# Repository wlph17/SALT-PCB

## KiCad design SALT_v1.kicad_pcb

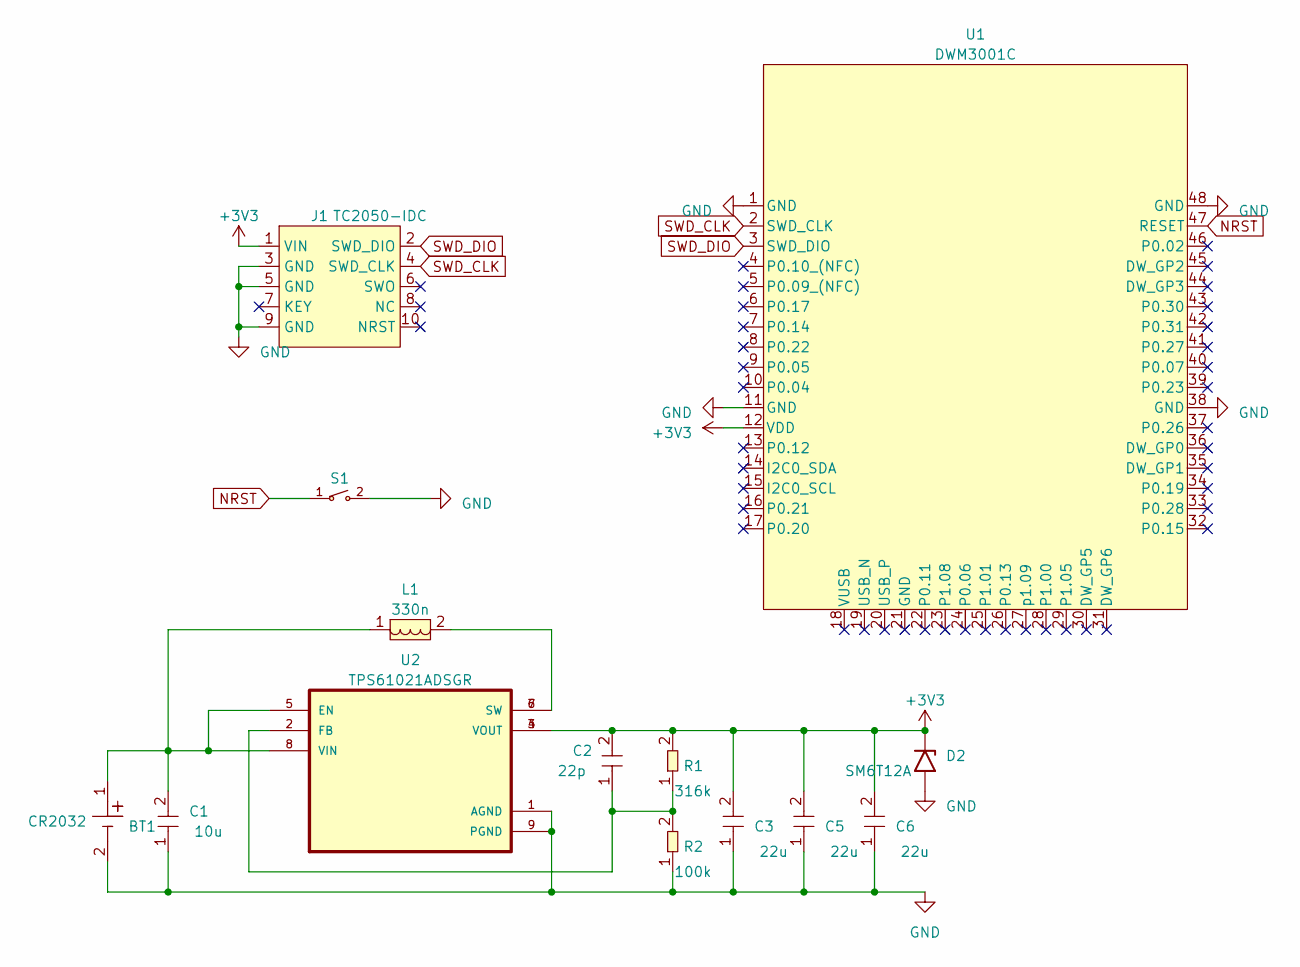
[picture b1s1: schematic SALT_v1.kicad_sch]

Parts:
BT1: CR2032; BAT_BHX1-2032-SM
C1: 10u; C_0603_1608Metric_Pad1.08x0.95mm_HandSolder
C2: 22p; C_0402_1005Metric_Pad0.74x0.62mm_HandSolder
C3, C5, C6: 22u; C_0603_1608Metric_Pad1.08x0.95mm_HandSolder
D2: SM6T12A; D_SMB
J1: TC2050-IDC
L1: 330n; IND_SRP4020TA-R33M
R1: 316k; R_0402_1005Metric_Pad0.72x0.64mm_HandSolder
R2: 100k; R_0402_1005Metric_Pad0.72x0.64mm_HandSolder
S1: SW_RS-032G05A3-SMRT
U1: DWM3001C
U2: TPS61021ADSGR

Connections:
+3V3: C2.2, C3.2, C5.2, C6.2, D2.1 (A1), J1.1 (VIN), R1.2, U1.12 (VDD), U2.3 (VOUT), U2.4 (VOUT)
GND: BT1.2, C1.1, C3.1, C5.1, C6.1, D2.2 (A2), J1.3 (GND), J1.5 (GND), J1.9 (GND), R2.1, S1.2, U1.1 (GND), U1.11 (GND), U1.38 (GND), U1.48 (GND), U2.1 (AGND), U2.9 (PGND), U2.9_1, U2.9_2
NRST: S1.1, U1.47 (RESET)
unnamed: L1.2, U2.6 (SW), U2.7 (SW)
unnamed: BT1.1, C1.2, L1.1, U2.5 (EN), U2.8 (VIN)
unnamed: C2.1, R1.1, R2.2, U2.2 (FB)
SWD_CLK: J1.4 (SWD_CLK), U1.2 (SWD_CLK)
SWD_DIO: J1.2 (SWD_DIO), U1.3 (SWD_DIO)

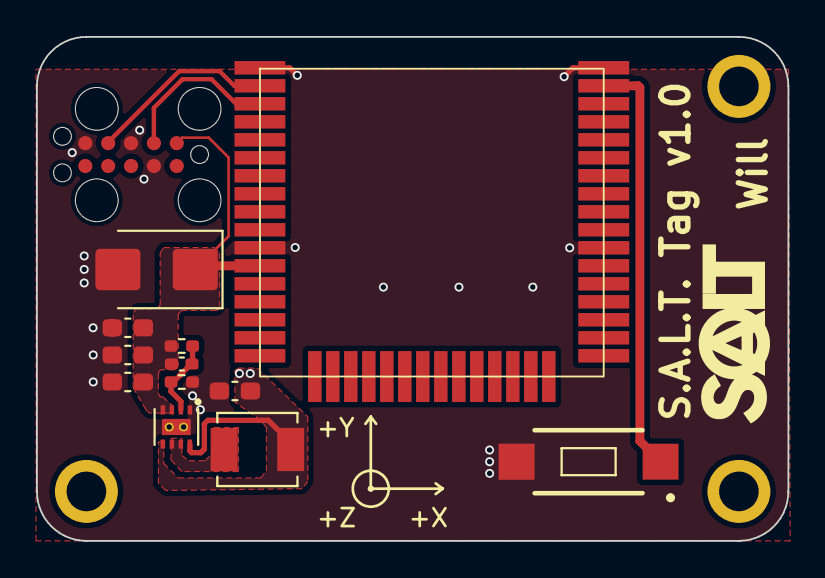
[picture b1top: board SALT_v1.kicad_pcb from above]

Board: 2 copper layers, 41.8 x 28.0 mm, 14 parts (1 on the bottom side), 8 nets.
